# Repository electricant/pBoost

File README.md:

# pBoost (pico-Boost)
Boost converter from 5V to 9V or 12V (user selectable). 1A maximum current

## The Project
I needed a way to power a small WiFi router from the same power supply that
powers a raspberry pi (5V 2A) so this board is born.

The router I plan to use has a power supply rated for 9V and 500mA so this is
my target deisgn goal.

Since the output voltage of the conveter is set by a resistor ratio I decided
to add a jumper-selectable output voltage. 12V were chosen because sometimes
routers come with 12V 1A power supplies so this design should be upgrade-proof.

NOTE: actually the maximum output current for 12V operation is a little lower
than 500mA. So be careful to check the current draw of your device.

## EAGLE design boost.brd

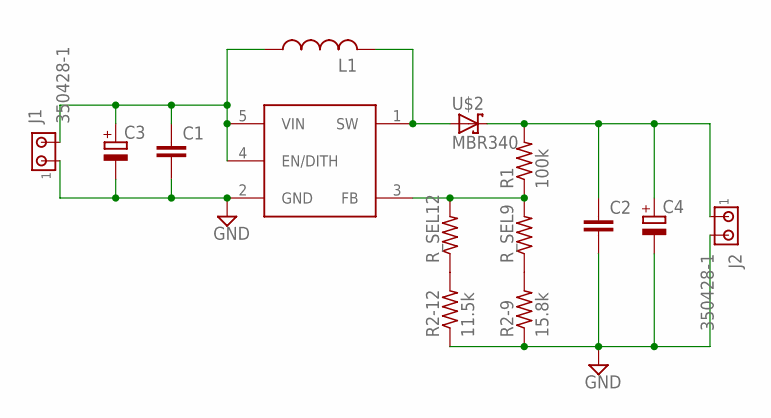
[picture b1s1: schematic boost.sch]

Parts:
C1, C2: C-EUC3216; C3216
C3, C4: CPOL-EUE1.8-4; E1,8-4
J1, J2: 350428-1
L1: L-US6000-XXX-RC; 6000-XXXX-RC
R1: 100k; M0805
R2-9: 15.8k; M0805
R2-12: 11.5k; M0805
R_SEL9, R_SEL12: R-US_R0402; R0402
U$1: MIC2250-2YD5; SOT23-5
U$2: MBR340; MBR340-V

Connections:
GND: C1.2, C2.2, C3.-, C4.-, J1.1, J2.2, R2-9.1, R2-12.1, U$1.2 (GND)
unnamed: L1.2, U$1.1 (SW), U$2.P$1 (A)
unnamed: R1.1, R_SEL9.2, R_SEL12.2, U$1.3 (FB)
unnamed: R2-12.2, R_SEL12.1
unnamed: R2-9.2, R_SEL9.1
VIN: C1.1, C3.+, J1.2, L1.1, U$1.4 (EN/DITH), U$1.5 (VIN)
VOUT: C2.1, C4.+, J2.1, R1.2, U$2.P$2 (C)

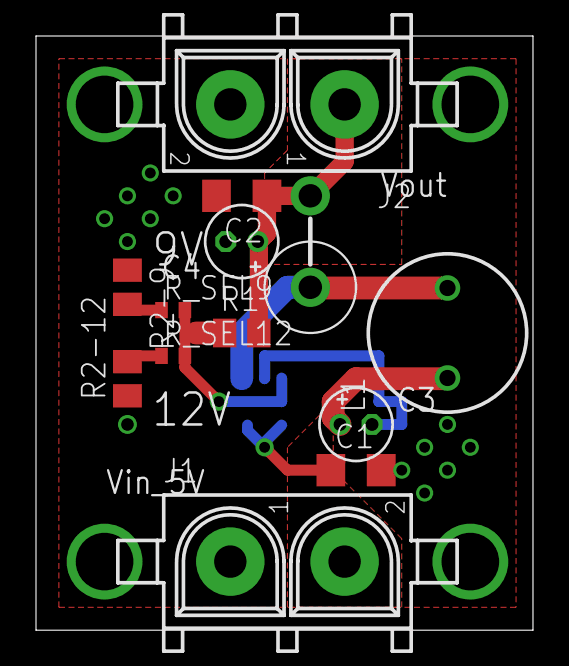
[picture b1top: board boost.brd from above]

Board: 2 copper layers, 27.6 x 33.0 mm, 14 parts (1 on the bottom side), 7 nets.

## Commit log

2016-02-17 Add datasheet folder
2016-02-17 Add schematic and board drawings
2016-02-17 Add generated gerber files
2016-02-17 Update readme with a note about maximum output current
